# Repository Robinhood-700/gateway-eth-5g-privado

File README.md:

# Gateway privado Ethernet-5G
Este proyecto contiene el diseño del PCB para la implementación de un gateway privado ethernet-dect, además del firmware correspondiente y un firmware simulado. Además contiene en la carpeta "resultados" la salida del proceso de build, flash y la ejecución del programa.
## Build
A continuación se describe el procedimiento para hacer el build del proyecto.
1. Cambiar de directorio a la carpeta padre del firmware:
```
// (desde la carpeta padre del proyecto)
cd firmware/esp32_gateway 
```
2. Activar el entorno ESP-IDF:
```
// En mi caso instalado en /opt. Cambia al directorio correspondiente $ESP_DIR
source /opt/esp/esp-idf/export.sh 
```
3. Realizar el comando build:
```
idf.py set-target esp32
idf.py reconfigure
idf.py fullclean build
```
### Para guardar el build en un archivo
Para guardar la salida del build en un fichero de texto, simplemente hice un pipe de la salida a un nuevo archivo .txt:
`idf.py fullclean build >> resultado_build.txt`
## Flash
1. Repetir pasos 1 y 2 del proceso build si no se ha ejecutado
```
// (desde la carpeta padre del proyecto)
cd firmware/esp32_gateway 
// En mi caso instalado en /opt. Cambia al directorio correspondiente $ESP_DIR
source /opt/esp/esp-idf/export.sh 
idf.py set-target esp32
idf.py reconfigure
```
2. Realizar el flash
```
// En el caso de mi portatil y la placa de desarrollo ESP32-Ethernet-Kit v1.2, el puerto es el
// /dev/ttyUSB1 y según la documentación de espressif, 115200 es el valor de baudios adecuado
idf.py -p /dev/ttyUSB1 -b 115200 flash monitor
// Este comando concatena el comando monitor con el flash para poder visualizar inmediatamente los resultados en pantalla.
```
### Para guardar el flash en un archivo
Igual que el build, simplemente hace falta un pipe en una terminal de bash:
`idf.py -p /dev/ttyUSB1 -b 115200 flash >> resultado_flash.txt`
### Para guardar la ejecución del programa en un archivo
`idf.py -p /dev/ttyUSB1 -b 115200 monitor >> resultado_monitor.txt`

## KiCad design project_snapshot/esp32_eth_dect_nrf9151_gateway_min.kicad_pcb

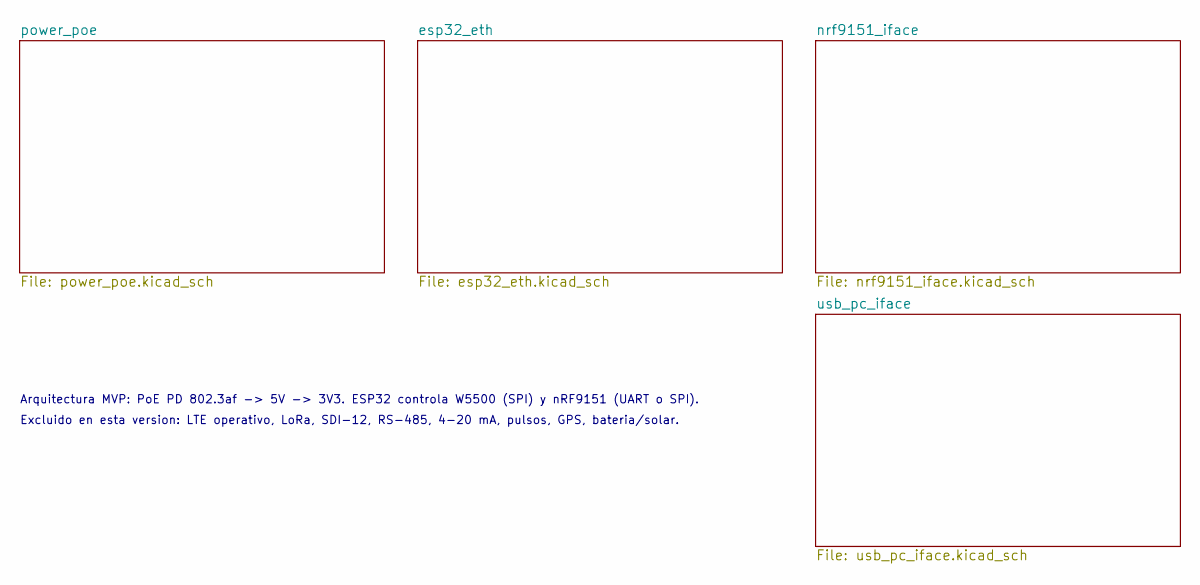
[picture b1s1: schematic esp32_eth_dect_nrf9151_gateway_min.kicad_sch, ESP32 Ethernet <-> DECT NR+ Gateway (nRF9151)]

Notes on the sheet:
Arquitectura MVP: PoE PD 802.3af -> 5V -> 3V3. ESP32 controla W5500 (SPI) y nRF9151 (UART o SPI).
Excluido en esta version: LTE operativo, LoRa, SDI-12, RS-485, 4-20 mA, pulsos, GPS, bateria/solar.

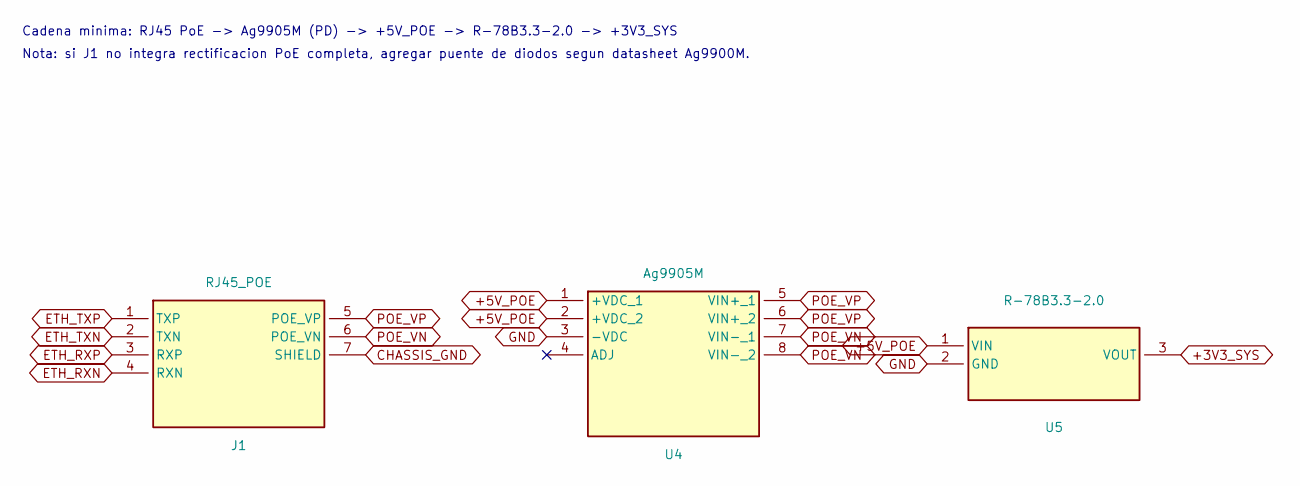
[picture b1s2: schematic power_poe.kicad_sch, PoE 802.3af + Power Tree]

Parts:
J1: RJ45_POE; RJ45_POE_MAG_PLACEHOLDER
U4: Ag9905M; POE_PD_8023AF_PLACEHOLDER
U5: R-78B3.3-2.0; BUCK_5V3V3_PLACEHOLDER

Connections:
+3V3_SYS: U5.3 (VOUT); also elsewhere on the board
+5V_POE: U4.1 (+VDC_1), U4.2 (+VDC_2), U5.1 (VIN); also elsewhere on the board
CHASSIS_GND: J1.7 (SHIELD); also elsewhere on the board
ETH_RXN: J1.4 (RXN); also elsewhere on the board
ETH_RXP: J1.3 (RXP); also elsewhere on the board
ETH_TXN: J1.2 (TXN); also elsewhere on the board
ETH_TXP: J1.1 (TXP); also elsewhere on the board
GND: U4.3 (-VDC), U5.2 (GND); also elsewhere on the board
POE_VN: J1.6 (POE_VN), U4.7 (VIN-_1), U4.8 (VIN-_2)
POE_VP: J1.5 (POE_VP), U4.5 (VIN+_1), U4.6 (VIN+_2)

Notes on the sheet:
Cadena minima: RJ45 PoE -> Ag9905M (PD) -> +5V_POE -> R-78B3.3-2.0 -> +3V3_SYS
Nota: si J1 no integra rectificacion PoE completa, agregar puente de diodos segun datasheet Ag9900M.

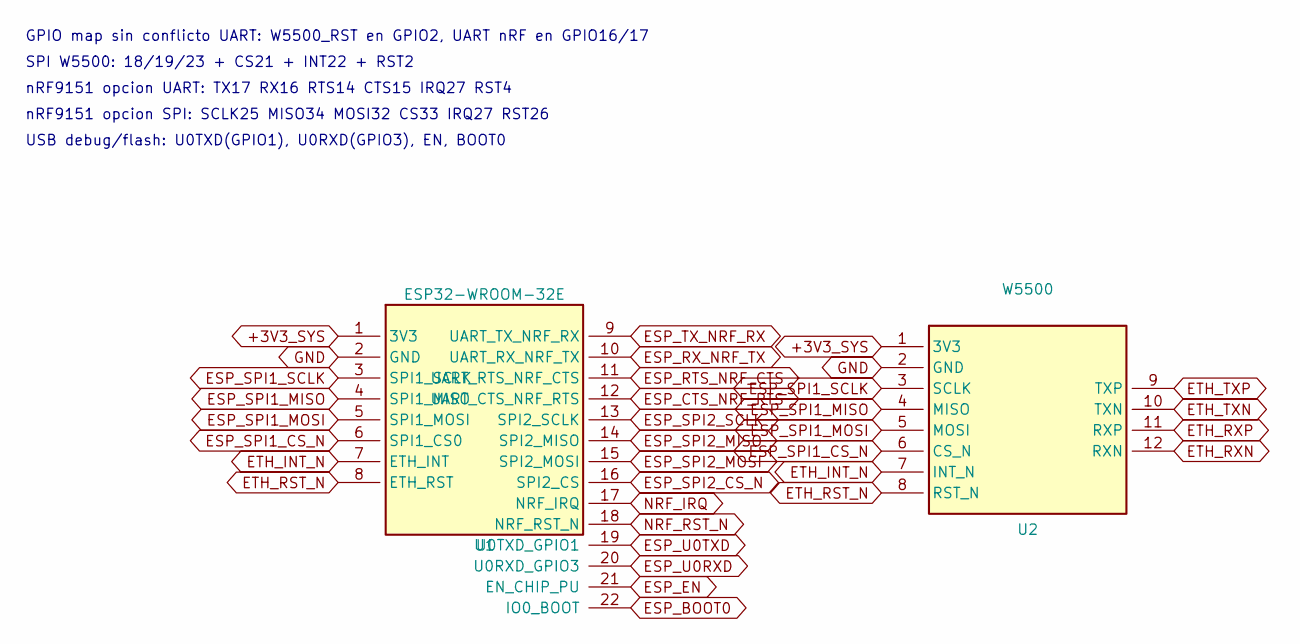
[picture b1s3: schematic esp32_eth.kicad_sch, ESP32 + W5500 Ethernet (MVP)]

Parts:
U1: ESP32-WROOM-32E; ESP32_WROOM_32E_PLACEHOLDER
U2: W5500; W5500_LQFP48_PLACEHOLDER

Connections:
+3V3_SYS: U1.1 (3V3), U2.1 (3V3); also elsewhere on the board
ESP_BOOT0: U1.22 (IO0_BOOT); also elsewhere on the board
ESP_CTS_NRF_RTS: U1.12 (UART_CTS_NRF_RTS); also elsewhere on the board
ESP_EN: U1.21 (EN_CHIP_PU); also elsewhere on the board
ESP_RTS_NRF_CTS: U1.11 (UART_RTS_NRF_CTS); also elsewhere on the board
ESP_RX_NRF_TX: U1.10 (UART_RX_NRF_TX); also elsewhere on the board
ESP_SPI1_CS_N: U1.6 (SPI1_CS0), U2.6 (CS_N)
ESP_SPI1_MISO: U1.4 (SPI1_MISO), U2.4 (MISO)
ESP_SPI1_MOSI: U1.5 (SPI1_MOSI), U2.5 (MOSI)
ESP_SPI1_SCLK: U1.3 (SPI1_SCLK), U2.3 (SCLK)
ESP_SPI2_CS_N: U1.16 (SPI2_CS); also elsewhere on the board
ESP_SPI2_MISO: U1.14 (SPI2_MISO); also elsewhere on the board
ESP_SPI2_MOSI: U1.15 (SPI2_MOSI); also elsewhere on the board
ESP_SPI2_SCLK: U1.13 (SPI2_SCLK); also elsewhere on the board
ESP_TX_NRF_RX: U1.9 (UART_TX_NRF_RX); also elsewhere on the board
ESP_U0RXD: U1.20 (U0RXD_GPIO3); also elsewhere on the board
ESP_U0TXD: U1.19 (U0TXD_GPIO1); also elsewhere on the board
ETH_INT_N: U1.7 (ETH_INT), U2.7 (INT_N)
ETH_RST_N: U1.8 (ETH_RST), U2.8 (RST_N)
ETH_RXN: U2.12 (RXN); also elsewhere on the board
ETH_RXP: U2.11 (RXP); also elsewhere on the board
ETH_TXN: U2.10 (TXN); also elsewhere on the board
ETH_TXP: U2.9 (TXP); also elsewhere on the board
GND: U1.2 (GND), U2.2 (GND); also elsewhere on the board
NRF_IRQ: U1.17 (NRF_IRQ); also elsewhere on the board
NRF_RST_N: U1.18 (NRF_RST_N); also elsewhere on the board

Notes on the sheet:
GPIO map sin conflicto UART: W5500_RST en GPIO2, UART nRF en GPIO16/17
SPI W5500: 18/19/23 + CS21 + INT22 + RST2
nRF9151 opcion UART: TX17 RX16 RTS14 CTS15 IRQ27 RST4
nRF9151 opcion SPI: SCLK25 MISO34 MOSI32 CS33 IRQ27 RST26
USB debug/flash: U0TXD(GPIO1), U0RXD(GPIO3), EN, BOOT0

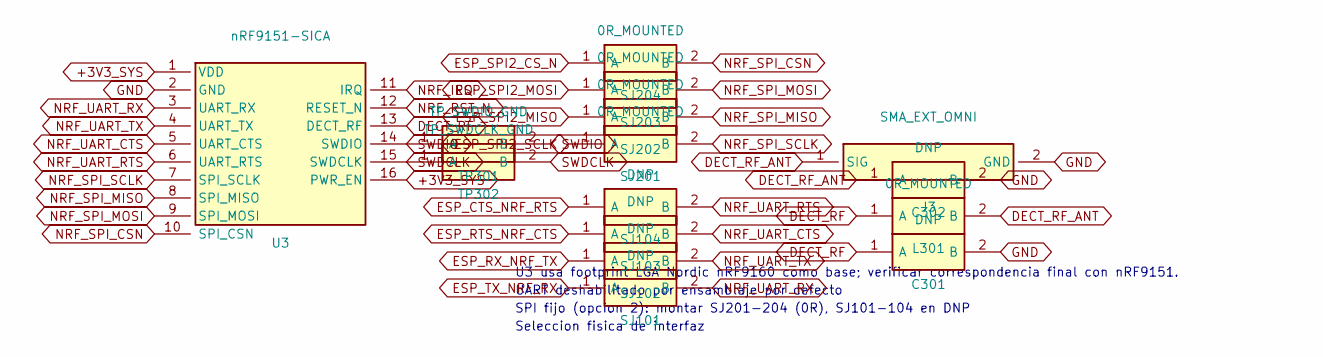
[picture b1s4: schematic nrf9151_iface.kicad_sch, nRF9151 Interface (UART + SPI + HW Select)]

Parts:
C301, C302: DNP; C_0402_1005Metric_RF
J3: SMA_EXT_OMNI; SMA_RF_PLACEHOLDER
L301: 0R_MOUNTED; L_0402_1005Metric
SJ101, SJ102, SJ103, SJ104: DNP; SJ_2PAD_PLACEHOLDER
SJ201, SJ202, SJ203, SJ204: 0R_MOUNTED; SJ_2PAD_PLACEHOLDER
TP301: TP_SWDIO_GND; PASSIVE_2PAD_PLACEHOLDER
TP302: TP_SWDCLK_GND; PASSIVE_2PAD_PLACEHOLDER
U3: nRF9151-SICA; NRF9151_SIP_PLACEHOLDER

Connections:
+3V3_SYS: U3.1 (VDD), U3.16 (PWR_EN); also elsewhere on the board
DECT_RF: C301.1 (A), L301.1 (A), U3.13 (DECT_RF)
DECT_RF_ANT: C302.1 (A), J3.1 (SIG), L301.2 (B)
ESP_CTS_NRF_RTS: SJ104.1 (A); also elsewhere on the board
ESP_RTS_NRF_CTS: SJ103.1 (A); also elsewhere on the board
ESP_RX_NRF_TX: SJ102.1 (A); also elsewhere on the board
ESP_SPI2_CS_N: SJ204.1 (A); also elsewhere on the board
ESP_SPI2_MISO: SJ202.1 (A); also elsewhere on the board
ESP_SPI2_MOSI: SJ203.1 (A); also elsewhere on the board
ESP_SPI2_SCLK: SJ201.1 (A); also elsewhere on the board
ESP_TX_NRF_RX: SJ101.1 (A); also elsewhere on the board
GND: C301.2 (B), C302.2 (B), J3.2 (GND), U3.2 (GND); also elsewhere on the board
NRF_IRQ: U3.11 (IRQ); also elsewhere on the board
NRF_RST_N: U3.12 (RESET_N); also elsewhere on the board
NRF_SPI_CSN: SJ204.2 (B), U3.10 (SPI_CSN)
NRF_SPI_MISO: SJ202.2 (B), U3.8 (SPI_MISO)
NRF_SPI_MOSI: SJ203.2 (B), U3.9 (SPI_MOSI)
NRF_SPI_SCLK: SJ201.2 (B), U3.7 (SPI_SCLK)
NRF_UART_CTS: SJ103.2 (B), U3.5 (UART_CTS)
NRF_UART_RTS: SJ104.2 (B), U3.6 (UART_RTS)
NRF_UART_RX: SJ101.2 (B), U3.3 (UART_RX)
NRF_UART_TX: SJ102.2 (B), U3.4 (UART_TX)
SWDCLK: TP302.1 (A), TP302.2 (B), U3.15 (SWDCLK)
SWDIO: TP301.1 (A), TP301.2 (B), U3.14 (SWDIO)

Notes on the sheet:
Seleccion fisica de interfaz
SPI fijo (opcion 2): montar SJ201-204 (0R), SJ101-104 en DNP
UART deshabilitado por ensamblaje por defecto
U3 usa footprint LGA Nordic nRF9160 como base; verificar correspondencia final con nRF9151.

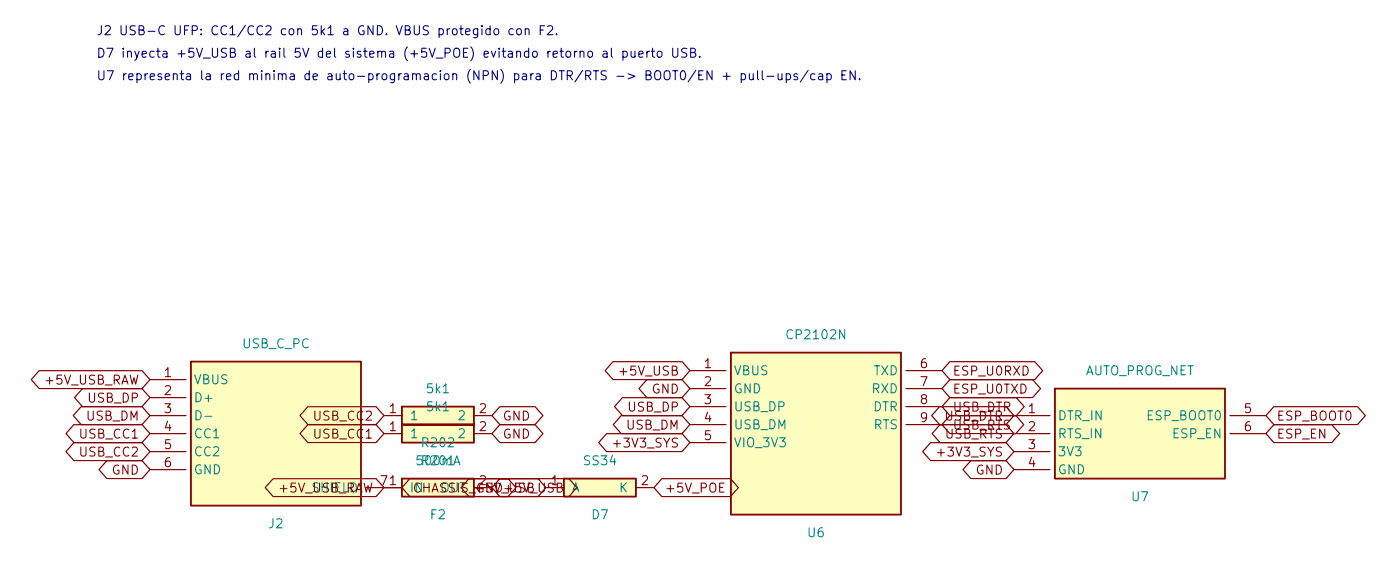
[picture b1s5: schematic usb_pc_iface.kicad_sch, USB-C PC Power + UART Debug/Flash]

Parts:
D7: SS34; PASSIVE_2PAD_PLACEHOLDER
F2: 500mA; PASSIVE_2PAD_PLACEHOLDER
J2: USB_C_PC; USB_C_PC_PLACEHOLDER
R201, R202: 5k1; PASSIVE_2PAD_PLACEHOLDER
U6: CP2102N; CP2102N_PLACEHOLDER
U7: AUTO_PROG_NET; AUTO_PROG_NET_PLACEHOLDER

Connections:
+3V3_SYS: U6.5 (VIO_3V3), U7.3 (3V3); also elsewhere on the board
+5V_POE: D7.2 (K); also elsewhere on the board
+5V_USB: D7.1 (A), F2.2 (OUT), U6.1 (VBUS)
+5V_USB_RAW: F2.1 (IN), J2.1 (VBUS)
CHASSIS_GND: J2.7 (SHIELD); also elsewhere on the board
ESP_BOOT0: U7.5 (ESP_BOOT0); also elsewhere on the board
ESP_EN: U7.6 (ESP_EN); also elsewhere on the board
ESP_U0RXD: U6.6 (TXD); also elsewhere on the board
ESP_U0TXD: U6.7 (RXD); also elsewhere on the board
GND: J2.6 (GND), R201.2, R202.2, U6.2 (GND), U7.4 (GND); also elsewhere on the board
USB_CC1: J2.4 (CC1), R201.1
USB_CC2: J2.5 (CC2), R202.1
USB_DM: J2.3 (D-), U6.4 (USB_DM)
USB_DP: J2.2 (D+), U6.3 (USB_DP)
USB_DTR: U6.8 (DTR), U7.1 (DTR_IN)
USB_RTS: U6.9 (RTS), U7.2 (RTS_IN)

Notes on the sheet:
J2 USB-C UFP: CC1/CC2 con 5k1 a GND. VBUS protegido con F2.
D7 inyecta +5V_USB al rail 5V del sistema (+5V_POE) evitando retorno al puerto USB.
U7 representa la red minima de auto-programacion (NPN) para DTR/RTS -> BOOT0/EN + pull-ups/cap EN.

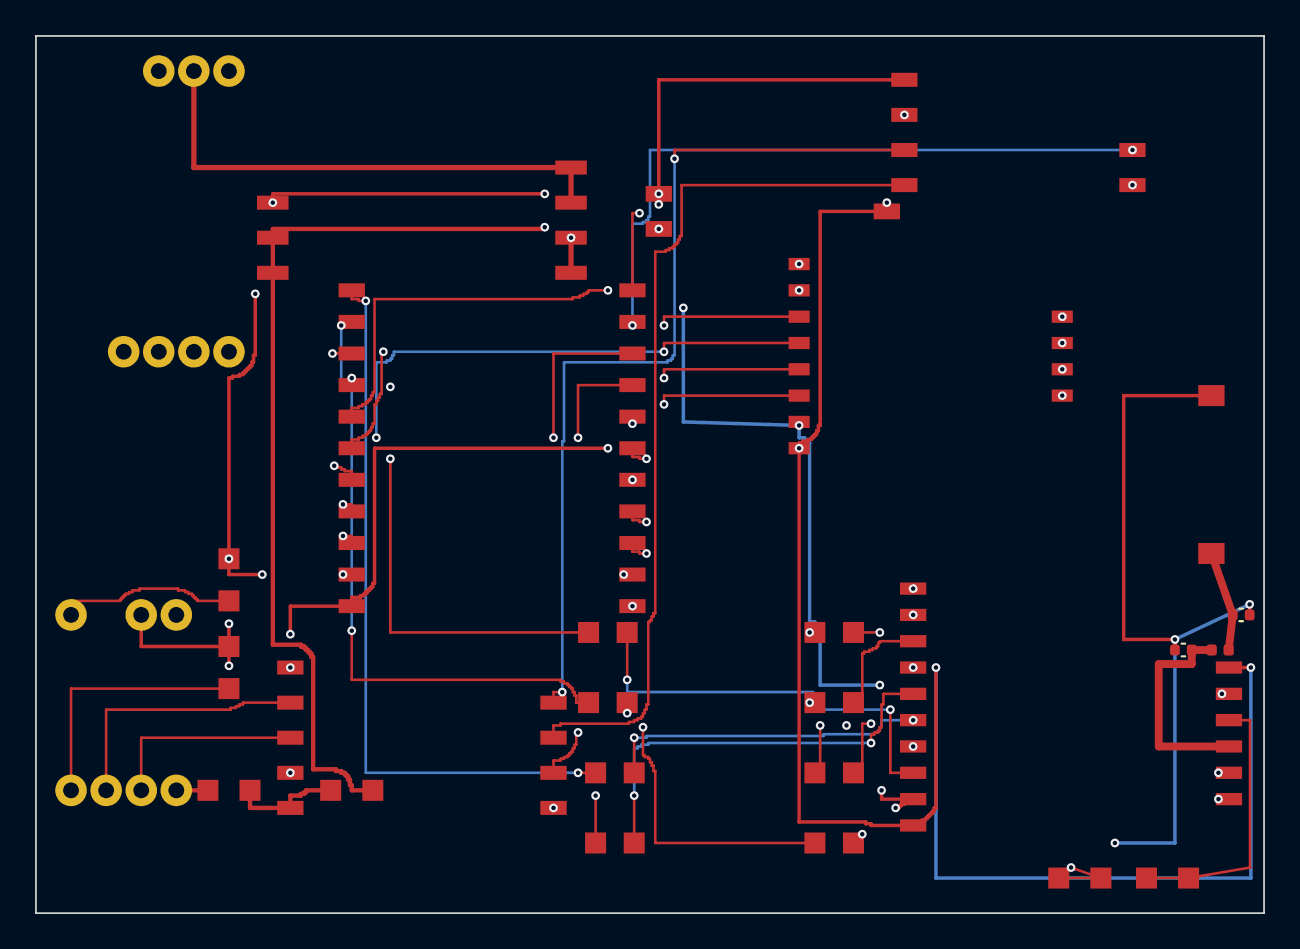
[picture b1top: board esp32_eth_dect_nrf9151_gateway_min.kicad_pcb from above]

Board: 4 copper layers, 70.0 x 50.0 mm, 27 parts (0 on the bottom side), 50 nets.

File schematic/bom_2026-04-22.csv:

"Refs","Value","Footprint","Qty","DNP"
"C301","DNP","gateway_min_local:C_0402_1005Metric_RF","1",""
"C302","DNP","gateway_min_local:C_0402_1005Metric_RF","1",""
"D7","SS34","PASSIVE_2PAD_PLACEHOLDER","1",""
"F2","500mA","PASSIVE_2PAD_PLACEHOLDER","1",""
"J1","RJ45_POE","RJ45_POE_MAG_PLACEHOLDER","1",""
"J2","USB_C_PC","USB_C_PC_PLACEHOLDER","1",""
"J3","SMA_EXT_OMNI","gateway_min_local:SMA_RF_PLACEHOLDER","1",""
"L301","0R_MOUNTED","Inductor_SMD:L_0402_1005Metric","1",""
"R201","5k1","PASSIVE_2PAD_PLACEHOLDER","1",""
"R202","5k1","PASSIVE_2PAD_PLACEHOLDER","1",""
"SJ101","DNP","SJ_2PAD_PLACEHOLDER","1",""
"SJ102","DNP","SJ_2PAD_PLACEHOLDER","1",""
"SJ103","DNP","SJ_2PAD_PLACEHOLDER","1",""
"SJ104","DNP","SJ_2PAD_PLACEHOLDER","1",""
"SJ201","0R_MOUNTED","SJ_2PAD_PLACEHOLDER","1",""
"SJ202","0R_MOUNTED","SJ_2PAD_PLACEHOLDER","1",""
"SJ203","0R_MOUNTED","SJ_2PAD_PLACEHOLDER","1",""
"SJ204","0R_MOUNTED","SJ_2PAD_PLACEHOLDER","1",""
"TP301","TP_SWDIO_GND","PASSIVE_2PAD_PLACEHOLDER","1",""
"TP302","TP_SWDCLK_GND","PASSIVE_2PAD_PLACEHOLDER","1",""
"U1","ESP32-WROOM-32E","ESP32_WROOM_32E_PLACEHOLDER","1",""
"U2","W5500","W5500_LQFP48_PLACEHOLDER","1",""
"U3","nRF9151-SICA","NRF9151_SIP_PLACEHOLDER","1",""
"U4","Ag9905M","POE_PD_8023AF_PLACEHOLDER","1",""
"U5","R-78B3.3-2.0","BUCK_5V3V3_PLACEHOLDER","1",""
"U6","CP2102N","CP2102N_PLACEHOLDER","1",""
"U7","AUTO_PROG_NET","AUTO_PROG_NET_PLACEHOLDER","1",""

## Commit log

2026-06-24 Subir proyecto correspondiente a la memoria final de prácticas
2026-06-24 corregir errores y actualizar salida de build
2026-06-24 Añadir README.md y código fuente de la memoria al repositorio
2026-06-24 Mover resultados a carpeta separada
2026-06-26 Añadir resultados de flash y flash monitor
2026-06-26 Añadir descripción de funciones
2026-06-26 Actualización memoria de prácticas
2026-06-26 Actualización memoria
